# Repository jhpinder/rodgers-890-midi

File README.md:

# Rodgers 890 Westminster MIDI Project

## Overview 

When installed and used correctly, this project:

- allows the 890 console to be used as a MIDI controller/receiver
- prevents the 890 from emitting any original analog sounds
- is non-destructive to the original analog tone generation
- gives the option to revert back to the original 890 analog tone generation

## Theory

The 890 reads in keyboards/pistons/stops using 4021 shift registers.
There are five data input chains:
- swell
- great
- pedal
- choir
- drawknobs/tablets

The 890 sets lamp outputs using 4094 shift registers into 2804 transistors.
There are six output chains:
- pipe chest
- swell/choir
- great
- pedal
- stops
- lamps

We will be using all the input chains since we are using almost every input, but only the sixth output for lamps since we are only driving lamps.

---
### MIDI Latency

Every MIDI note command take approximately 1 millisecond to transmit.
We have over 90 lamps that can be changed at any time from the MIDI input.
This means if there are 50 lamp changes, it will take at least 50ms before the processor empties out the MIDI receive queue.
The acceptable time between note refreshing is 10ms.
If the organist is playing notes constantly and presses a piston that changes more than 10 lamps, there will theoretically be a delay before the next note refresh.

There are several solutions to this issue.

### *Solution 1: Hardware separation of keyboards and stops*

We can use one processor and MIDI port to process all the keyboards and their corresponding pistons and another processor and MIDI port to handle all the stops and lamps.
USB-MIDI interfaces sometimes feature multiple MIDI ports which are completely independent of each other.
This would allow one processor to dedicate its MIDI port to sending keyboard/piston note commands with no connection to the stops/lamps.
The other processor would be able to spend as much time as needed to receive MIDI notes and update lamps.

### *Solution 2 (**Current**): MIDI receive processing limits*

During each loop, we check if `MIDI.read()` is true (if there is an incoming message).
We continue to process MIDI messages in each loop until the incoming queue is empty.
However, if we receive more than 10 note commands at once, that breaks the limit of 10ms.
Before each time we check for an incoming message, we check to see if more than 10ms has elapsed since the last keyboard scan.
We do not update the lamps until the entire message queue has been emptied so as not to possibly create a ripple effect.
This complicates the code a little bit but allows the entire organ to run off of one MIDI port.
The logic for determining if more than the allowed amount of time has passed since the last keyboard read can be bypassed by connecting pin 3 to ground. For this to take effect, the arduino must be reset.

---
### Drawknobs and Tilt Tabs

Each drawknob and tilt tab has a lamp, an "on" contact, and an "off" contact.
When you turn the stop on, you pull the drawknob and release.
The lamp turns on and the drawknob moves back to its default center position.
The same goes for pushing the stop to turn it off.
The act of pushing or pulling a stop physically changes the state of the 2804 transistor and also changes the state of the corresponding 4021 shift register.
This means that there is a possibility of echoing a MIDI note on or note off command coming from the organ software.

To solve this issue, when receiving MIDI note commands, we `or` the "previous state" word with any reveiced MIDI note command. When scanning for changes on the next loop, those changes that are now read in do not trigger new MIDI note commands to be sent back to the organ software.

---
### I/O Chain <-> MIDI

There are 5 input chains and one output chain that interface with MIDI. Four of the input chains contain a keyboard but they do not start at the 36th position, rather the 33rd for manuals and 65th for pedals.
If we output the raw chain position to MIDI, there will be a transposition required by the organ software.
Instead, we have opted to shift the positions of the input chain before we send out the MIDI note events.
This also means that the pistons associated with each keyboard are shifted as well.
To further complicate the matter, the lamps associated with each piston are not lined up 1:1 in an output chain with each input piston.
Instead, the piston lamps are added on to the end of the drawknob lamp output chain.

We have developed two functions that interface between the I/O chains and MIDI events.
The function `chainToMidi()` accepts the input chain number and bit address, and returns the corresponding MIDI channel and note number.
The function `midiToChain()` accepts a MIDI channel and note, and returns the corresponding output chain number and bit address.

This allows us to convert from the I/O chain to MIDI note/channel and back very quickly without having to implement a lookup table.

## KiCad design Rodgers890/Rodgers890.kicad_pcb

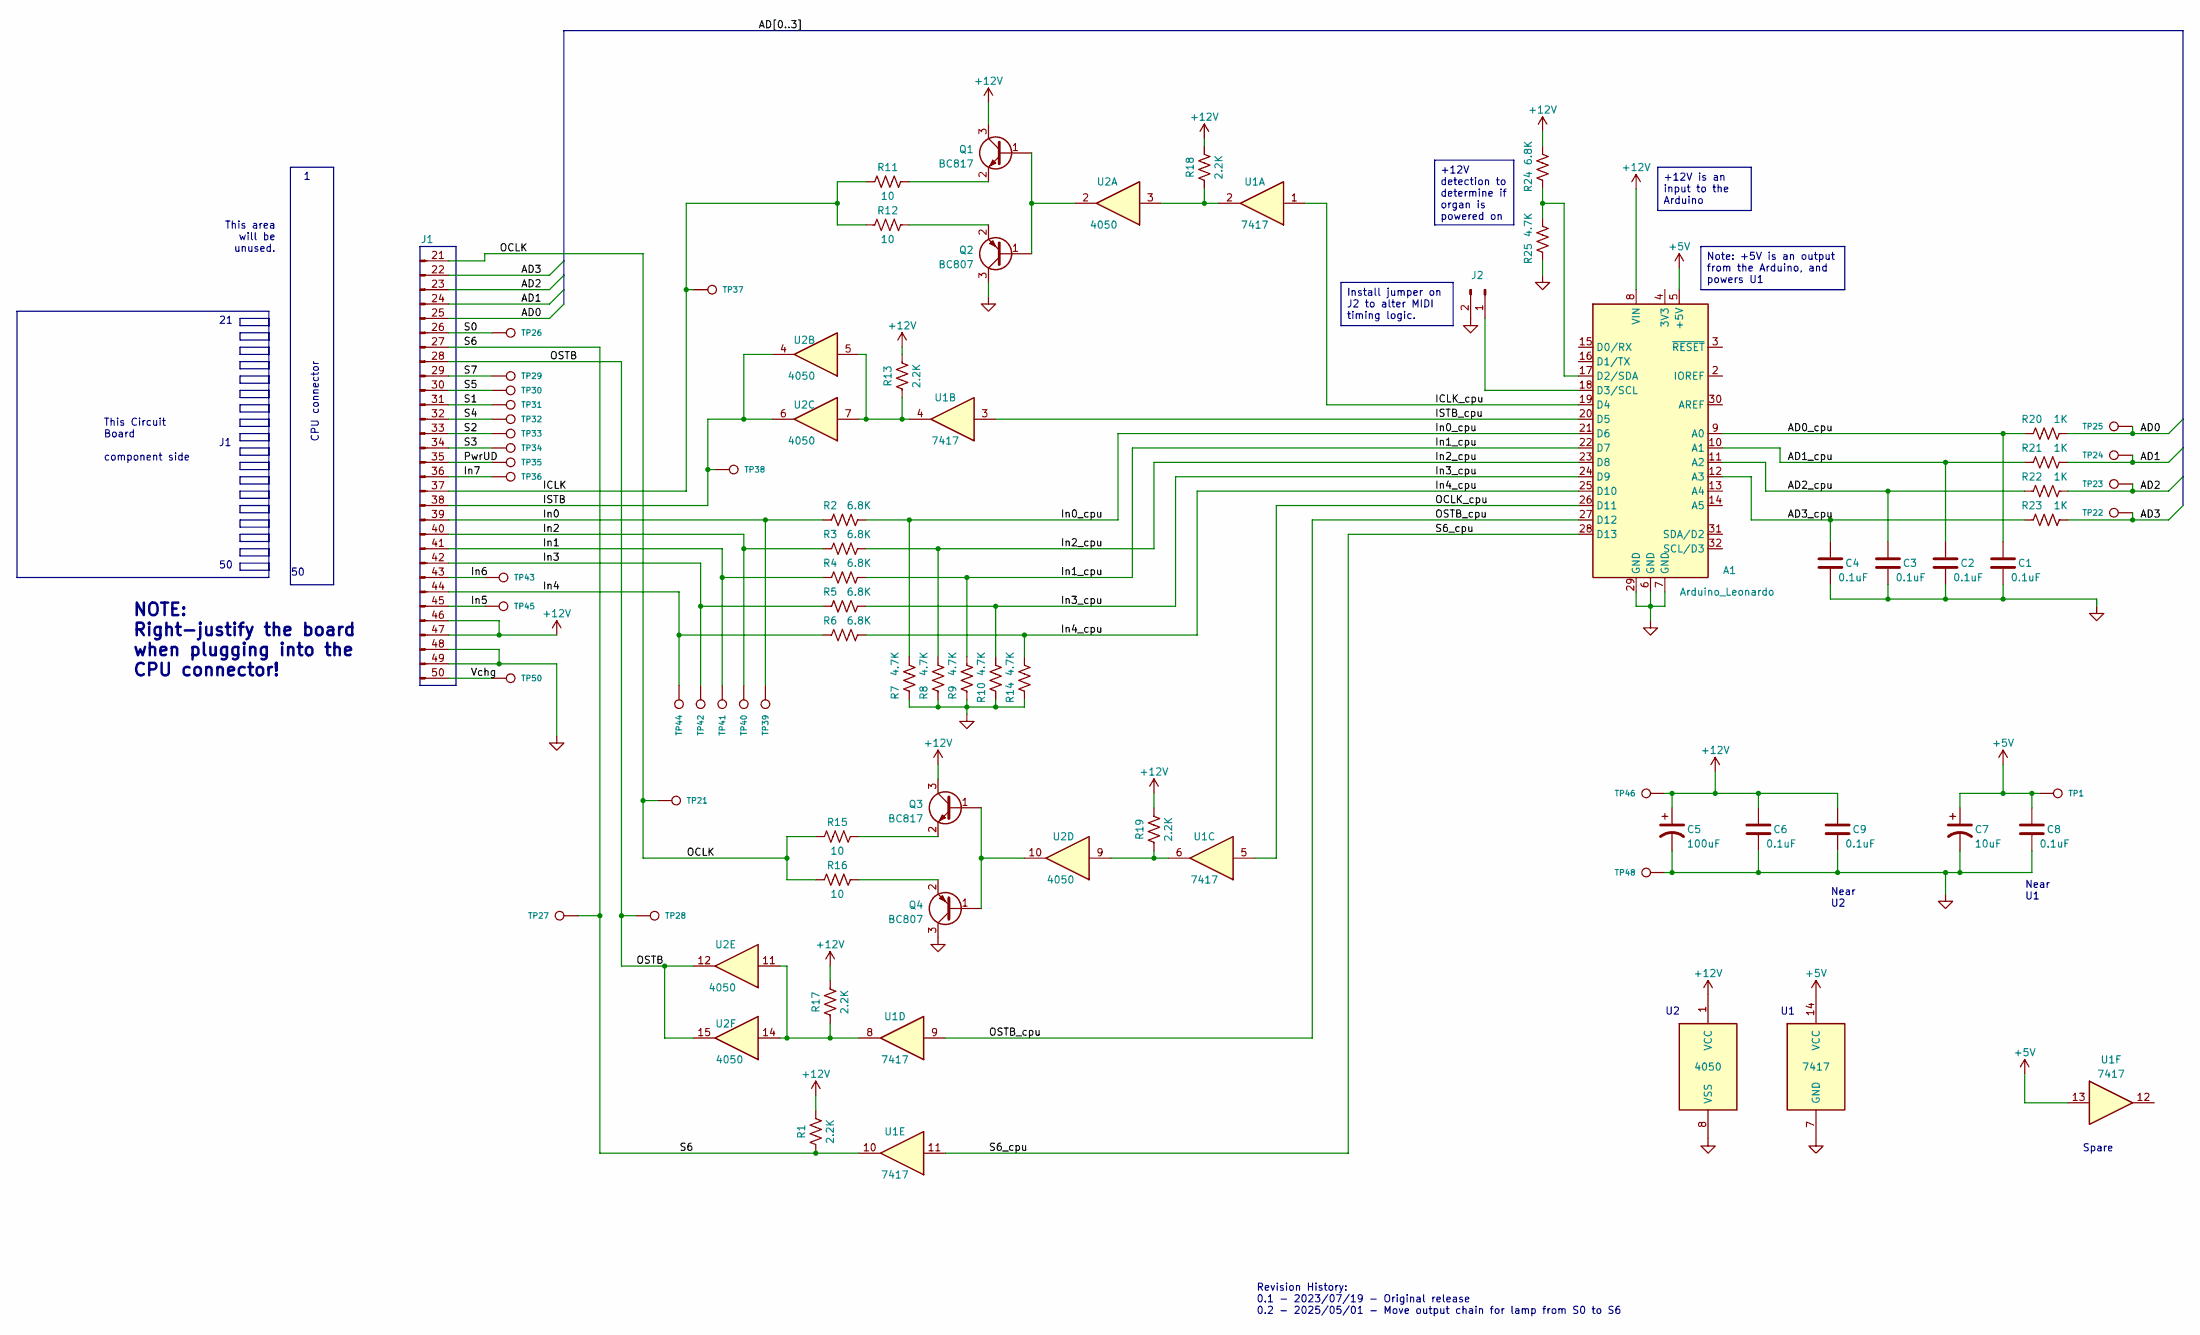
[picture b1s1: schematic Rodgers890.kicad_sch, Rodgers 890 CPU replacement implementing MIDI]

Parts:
A1: Arduino_Leonardo; Arduino_UNO_R3
C1, C2, C3, C4, C6, C8, C9: 0.1uF; C_0603_1608Metric_Pad1.08x0.95mm_HandSolder
C5: 100uF; CP_Radial_D12.5mm_P7.50mm
C7: 10uF; C_1206_3216Metric_Pad1.33x1.80mm_HandSolder
J1: Conn_01x30_Pin; CardEdge_125_30_of_50
J2: Conn_01x02_Pin; PinHeader_1x02_P2.54mm_Vertical
Q1, Q3: BC817; SOT-23
Q2, Q4: BC807; SOT-23
R1, R13, R17, R18, R19: 2.2K; R_0603_1608Metric_Pad0.98x0.95mm_HandSolder
R2, R3, R4, R5, R6, R24: 6.8K; R_0603_1608Metric_Pad0.98x0.95mm_HandSolder
R7, R8, R9, R10, R14, R25: 4.7K; R_0603_1608Metric_Pad0.98x0.95mm_HandSolder
R11, R12, R15, R16: 10; R_0603_1608Metric_Pad0.98x0.95mm_HandSolder
R20, R21, R22, R23: 1K; R_0603_1608Metric_Pad0.98x0.95mm_HandSolder
TP1, TP21, TP22, TP23, TP24, TP25, TP26, TP27, TP28, TP29, TP30, TP31, TP32, TP33, TP34, TP35, TP36, TP37, TP38, TP39, TP40, TP41, TP42, TP43, TP44, TP45, TP46, TP48, TP50: TestPoint; TestPoint_THTPad_2.0x2.0mm_Drill1.0mm
U1: 7417; SOIC-14_3.9x8.7mm_P1.27mm
U2: 4050; SOIC-16_3.9x9.9mm_P1.27mm

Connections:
+5V: A1.5 (+5V), C7.1, C8.1, TP1.1, U1.13, U1.14 (VCC)
+12V: A1.8 (VIN), C5.1, C6.1, C9.1, J1.46, J1.47, Q1.3 (C), Q3.3 (C), R1.2, R13.2, R17.2, R18.2, R19.2, R24.2, TP46.1, U2.1 (VCC)
/AD0: J1.25, R20.2, TP25.1
/AD0_cpu: A1.9 (A0), C1.1, R20.1
/AD1: J1.24, R21.2, TP24.1
/AD1_cpu: A1.10 (A1), C2.1, R21.1
/AD2: J1.23, R22.2, TP23.1
/AD2_cpu: A1.11 (A2), C3.1, R22.1
/AD3: J1.22, R23.2, TP22.1
/AD3_cpu: A1.12 (A3), C4.1, R23.1
/ICLK: J1.37, R11.1, R12.1, TP37.1
/ICLK_cpu: A1.19 (D4), U1.1
/ISTB: J1.38, TP38.1, U2.4, U2.6
/ISTB_cpu: A1.20 (D5), U1.3
/In0: J1.39, R2.1, TP39.1
/In0_cpu: A1.21 (D6), R2.2, R7.2
/In1: J1.41, R4.1, TP41.1
/In1_cpu: A1.22 (D7), R4.2, R9.2
/In2: J1.40, R3.1, TP40.1
/In2_cpu: A1.23 (D8), R3.2, R8.2
/In3: J1.42, R5.1, TP42.1
/In3_cpu: A1.24 (D9), R5.2, R10.2
/In4: J1.44, R6.1, TP44.1
/In4_cpu: A1.25 (D10), R6.2, R14.2
/In5: J1.45, TP45.1
/In6: J1.43, TP43.1
/In7: J1.36, TP36.1
/OCLK: J1.21, R15.1, R16.1, TP21.1
/OCLK_cpu: A1.26 (D11), U1.5
/OSTB: J1.28, TP28.1, U2.12, U2.15
/OSTB_cpu: A1.27 (D12), U1.9
/PwrUD: J1.35, TP35.1
/S0: J1.26, TP26.1
/S1: J1.31, TP31.1
/S2: J1.33, TP33.1
/S3: J1.34, TP34.1
/S4: J1.32, TP32.1
/S5: J1.30, TP30.1
/S6: J1.27, R1.1, TP27.1, U1.10
/S6_cpu: A1.28 (D13), U1.11
/S7: J1.29, TP29.1
/Vchg: J1.50, TP50.1
GND: A1.6 (GND), A1.7 (GND), A1.29 (GND), C1.2, C2.2, C3.2, C4.2, C5.2, C6.2, C7.2, C8.2, C9.2, J1.48, J1.49, J2.2, Q2.3 (C), Q4.3 (C), R7.1, R8.1, R9.1, R10.1, R14.1, R25.1, TP48.1, U1.7 (GND), U2.8 (VSS)
unnamed: A1.17 (D2/SDA), R24.1, R25.2
unnamed: A1.18 (D3/SCL), J2.1
unnamed: Q1.1 (B), Q2.1 (B), U2.2
unnamed: Q1.2 (E), R11.2
unnamed: Q2.2 (E), R12.2
unnamed: Q3.1 (B), Q4.1 (B), U2.10
unnamed: Q3.2 (E), R15.2
unnamed: Q4.2 (E), R16.2
unnamed: R13.1, U1.4, U2.5, U2.7
unnamed: R17.1, U1.8, U2.11, U2.14
unnamed: R18.1, U1.2, U2.3
unnamed: R19.1, U1.6, U2.9

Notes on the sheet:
Near U2
This Circuit Board component side
Spare
This area will be unused.
NOTE: Right-justify the board when plugging into the CPU connector!
Near U1
CPU connector
Revision History: 0.1 - 2023/07/19 - Original release 0.2 - 2025/05/01 - Move output chain for lamp from S0 to S6
+12V detection to determine if organ is powered on
Install jumper on J2 to alter MIDI timing logic.
Note: +5V is an output from the Arduino, and powers U1
+12V is an input to the Arduino

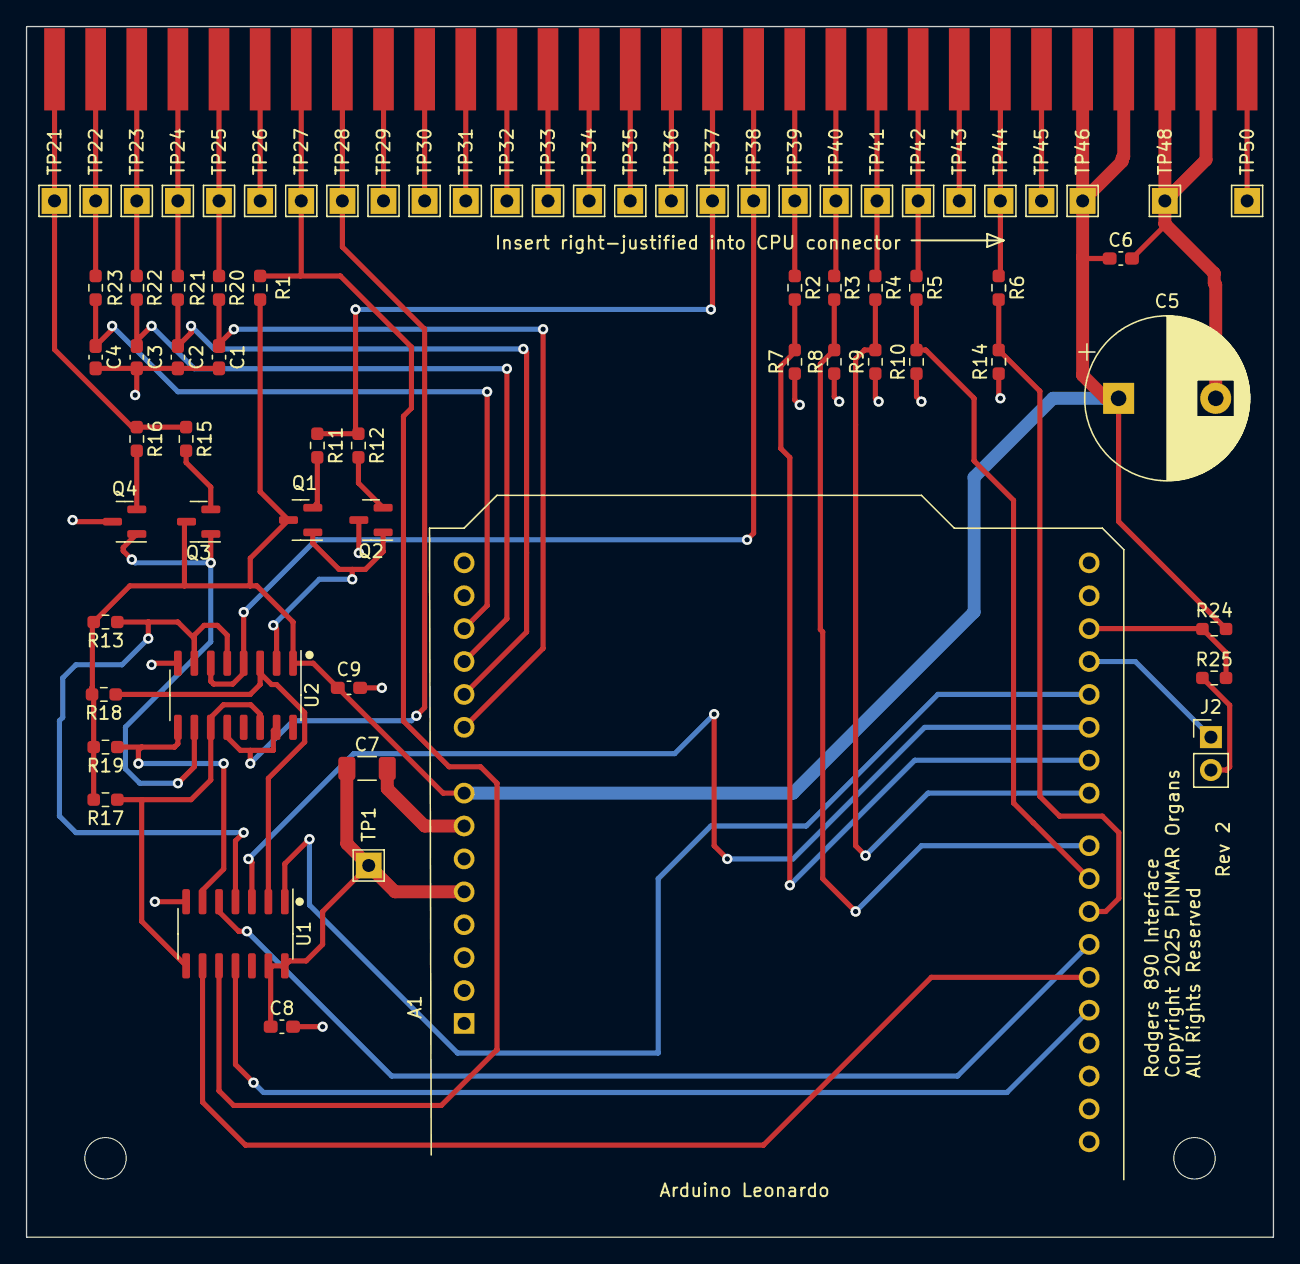
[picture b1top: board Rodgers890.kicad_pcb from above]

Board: 2 copper layers, 96.3 x 93.5 mm, 72 parts (0 on the bottom side), 55 nets.

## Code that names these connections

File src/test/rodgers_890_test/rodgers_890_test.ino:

#define POWER_DETECT 2
#define RECEIVE_MIDI_LIMIT_PIN 3

#define ICLK 4
#define ISTB 5
#define I0 6   // swell
#define I1 7   // great
#define I2 8   // pedal
#define I3 9   // drawknobs
#define I4 10  // choir

#define OCLK 11
#define OSTB 12
#define O6 13

#define ISTB_DELAY 1  // Microseconds
#define ICLK_DELAY 1

#define OSTB_DELAY 1
#define OCLK_DELAY 1

int inputPins[] = { I0, I1, I2, I3, I4, POWER_DETECT };
int inputPullupPins[] = { RECEIVE_MIDI_LIMIT_PIN };
int outputPins[] = { ICLK, ISTB, OCLK, OSTB, O6 };
bool cycleMode;

void setup() {
  for (int pin : inputPins) {
    pinMode(pin, INPUT);
  }
  for (int pin : inputPullupPins) {
    pinMode(pin, INPUT_PULLUP);
  }
  for (int pin : outputPins) {
    pinMode(pin, OUTPUT);
  }
}

void loop() {
  cycleMode = !digitalRead(RECEIVE_MIDI_LIMIT_PIN);
  if (cycleMode) {
    for (int pin : outputPins) {
      digitalWrite(pin, HIGH);
      delay(250);
      digitalWrite(pin, LOW);
      delay(250);
    }
  } else {
    digitalWrite(ISTB, HIGH);
    delayMicroseconds(ISTB_DELAY);
    digitalWrite(ISTB, LOW);

    digitalWrite(OSTB, HIGH);
    delayMicroseconds(OSTB_DELAY);
    digitalWrite(OSTB, LOW);

    digitalWrite(ICLK, HIGH);
    delayMicroseconds(ICLK_DELAY);
    digitalWrite(ICLK, LOW);

    digitalWrite(OCLK, HIGH);
    delayMicroseconds(OCLK_DELAY);
    digitalWrite(OCLK, LOW);
    delay(1000);
  }
}

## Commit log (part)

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2023-07-19 initial thoughts
2023-07-19 midi usb on leonardo
2023-07-19 Create Rodgers890.pdf
    Schematic for CPU board replacement
2023-07-19 using midi-chain lookup functions
2023-07-20 added incoming midi limit bypass
2023-07-20 Add J2 to select Midi mode to schematic. Update TP ref designators to match card edge pin numbers. Add inital proposed board layout for review.
2023-07-20 added power detect logic
2023-07-20 Add +12V detect and mounting holes
2023-07-22 Update schematic to match production PCB
2023-07-22 Remove prelim placement file (see full PCB design for those details)
2023-07-22 Add KiCad files representing the first PCB revision
2023-07-25 added basic I/O test, separated into folders
2023-07-29 installed
2023-07-29 print received MIDI on stops
2023-07-30 added analog inputs on CC 7
2023-08-15 gt/ped manual and toe pistons now send identical messages
2024-06-20 Add minimal power config
2025-05-01 Address Issue #4: Wrong output chain used, for PCB. Revision marking on PCB is "Rev 2".
2025-05-01 Address Issue #4: Wrong output chain used, for schematic only. Revision marking on schematic becomes “Rev 0.2”
2025-05-08 Ready for first schematic review with James

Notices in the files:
Rodgers890/Rodgers890.kicad_pcb:
Copyright 2025 PINMAR Organs
All Rights Reserved
